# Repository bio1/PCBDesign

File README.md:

# PCBDesign
Babs Ogunbanwo
ENGI 301

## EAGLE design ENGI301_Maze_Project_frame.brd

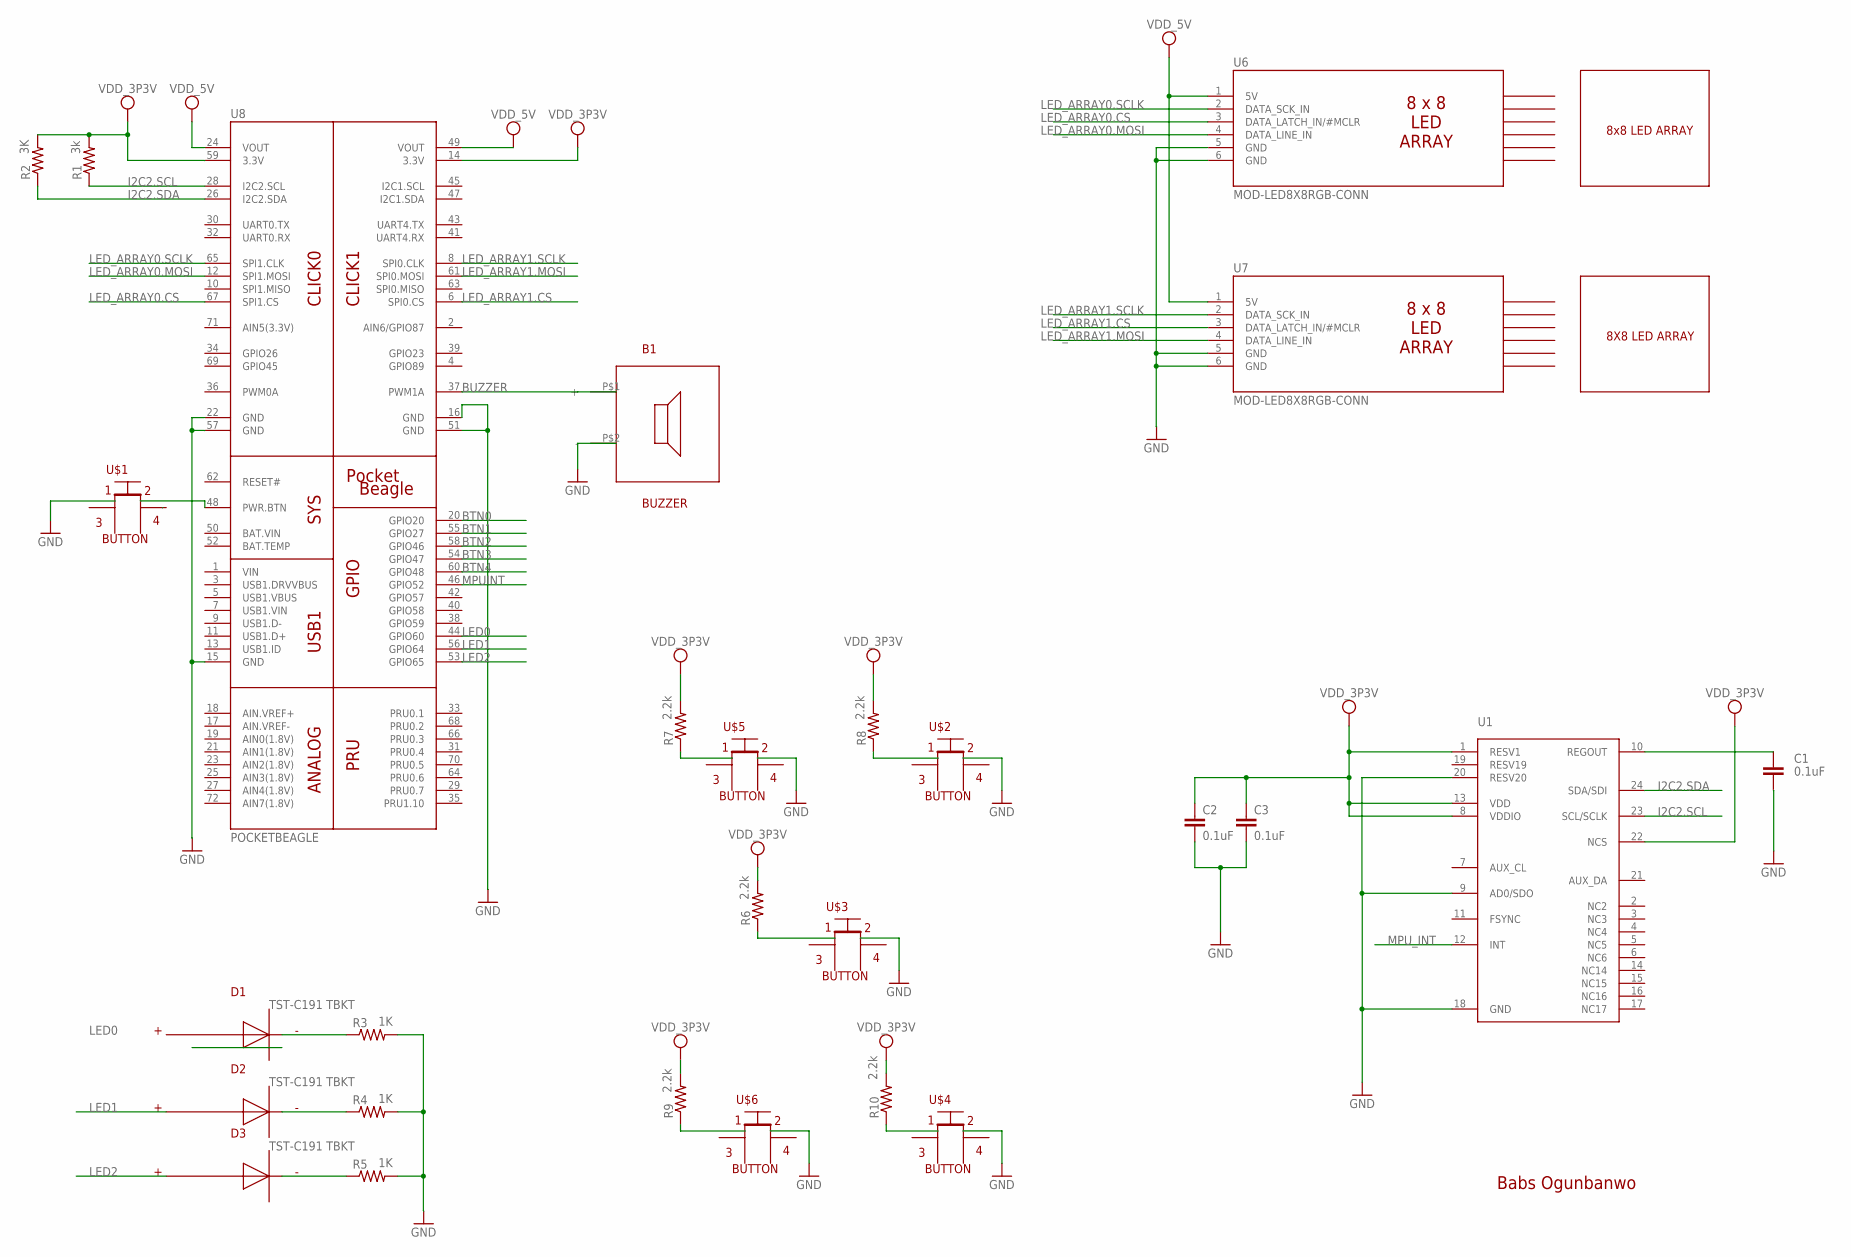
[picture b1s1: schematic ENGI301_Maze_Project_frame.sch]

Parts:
B1: BUZZER
C1, C2, C3: 0.1uF; C0603
D1, D2, D3: TST-C191 TBKT; LED
R1: 3k; R0603
R2: 3K; R0603
R3, R4, R5: 1K; R0603
R6, R7, R8, R9, R10: 2.2k; R0603
U1: MPU-9250; QFN-3MMX3MM
U6, U7: MOD-LED8X8RGB-CONN; FE06W
U8: POCKETBEAGLE
U$1, U$2, U$3, U$4, U$5, U$6: BUTTON

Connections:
BTN0: U8.20 (GPIO20)
BTN1: U8.55 (GPIO27)
BTN2: U8.58 (GPIO46)
BTN3: U8.54 (GPIO47)
BTN4: U8.60 (GPIO48)
BUZZER: B1.P$1 (+), U8.37 (PWM1A)
GND: B1.P$2 (-), C1.2, C2.2, C3.2, R3.2, R4.2, R5.2, U1.9 (AD0/SDO), U1.20 (RESV20), U6.5 (GND), U6.6 (GND), U7.5 (GND), U7.6 (GND), U8.15 (GND), U8.16 (GND), U8.22 (GND), U8.51 (GND), U8.57 (GND), U$1.P$1 (1), U$2.P$2 (2), U$3.P$2 (2), U$4.P$2 (2), U$5.P$2 (2), U$6.P$2 (2)
I2C2.SCL: R1.1, U1.23 (SCL/SCLK), U8.28 (I2C2.SCL)
I2C2.SDA: R2.1, U1.24 (SDA/SDI), U8.26 (I2C2.SDA)
LED0: D1.+, U8.44 (GPIO60)
LED1: D2.+, U8.56 (GPIO64)
LED2: D3.+, U8.53 (GPIO65)
LED_ARRAY0.CS: U6.3 (DATA_LATCH_IN/#MCLR), U8.67 (SPI1.CS)
LED_ARRAY0.MOSI: U6.4 (DATA_LINE_IN), U8.12 (SPI1.MOSI)
LED_ARRAY0.SCLK: U6.2 (DATA_SCK_IN), U8.65 (SPI1.CLK)
LED_ARRAY1.CS: U7.3 (DATA_LATCH_IN/#MCLR), U8.6 (SPI0.CS)
LED_ARRAY1.MOSI: U7.4 (DATA_LINE_IN), U8.61 (SPI0.MOSI)
LED_ARRAY1.SCLK: U7.2 (DATA_SCK_IN), U8.8 (SPI0.CLK)
MPUINT: U8.46 (GPIO52)
MPU_INT: U1.12 (INT)
unnamed: C1.1, U1.10 (REGOUT)
unnamed: U8.48 (PWR.BTN), U$1.P$2 (2)
unnamed: D1.-, R3.1
unnamed: D2.-, R4.1
unnamed: D3.-, R5.1
unnamed: R7.1, U$5.P$1 (1)
unnamed: R8.1, U$2.P$1 (1)
unnamed: R6.1, U$3.P$1 (1)
unnamed: R9.1, U$6.P$1 (1)
unnamed: R10.1, U$4.P$1 (1)
SYS_VDD1_3P3V: C2.1, C3.1, R1.2, R2.2, R6.2, R7.2, R8.2, R9.2, R10.2, U1.1 (RESV1), U1.8 (VDDIO), U1.13 (VDD), U1.22 (NCS), U6.1 (5V), U7.1 (5V), U8.14 (3.3V), U8.24 (VOUT), U8.49 (VOUT), U8.59 (3.3V)

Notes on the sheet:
Babs Ogunbanwo
8x8 LED ARRAY
8X8 LED ARRAY

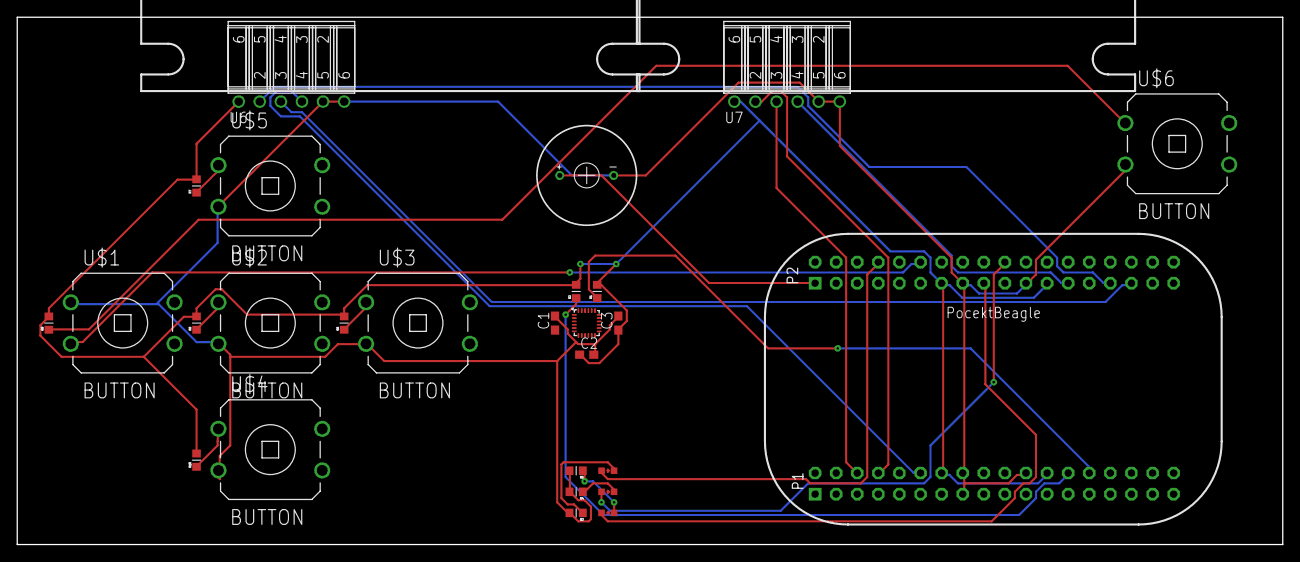
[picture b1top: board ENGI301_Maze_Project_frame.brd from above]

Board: 4 copper layers, 152.4 x 63.5 mm, 31 parts (0 on the bottom side), 24 nets.

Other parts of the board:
U$7, U$8, U$9, U$10: MOD-LED8X8RGB

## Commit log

2018-04-04 Initial Device EAGLE
2018-04-09 Add files via upload
    Final PCB Library Project #2a
2018-04-21 Add files via upload
    Project 2b PCB board
2018-04-21 Add files via upload
    Pictures of routed board and schematic
